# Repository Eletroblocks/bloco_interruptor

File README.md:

# interruptor
PERMITE ou INTERROMPE a transmissão de energia para os blocos seguintes.

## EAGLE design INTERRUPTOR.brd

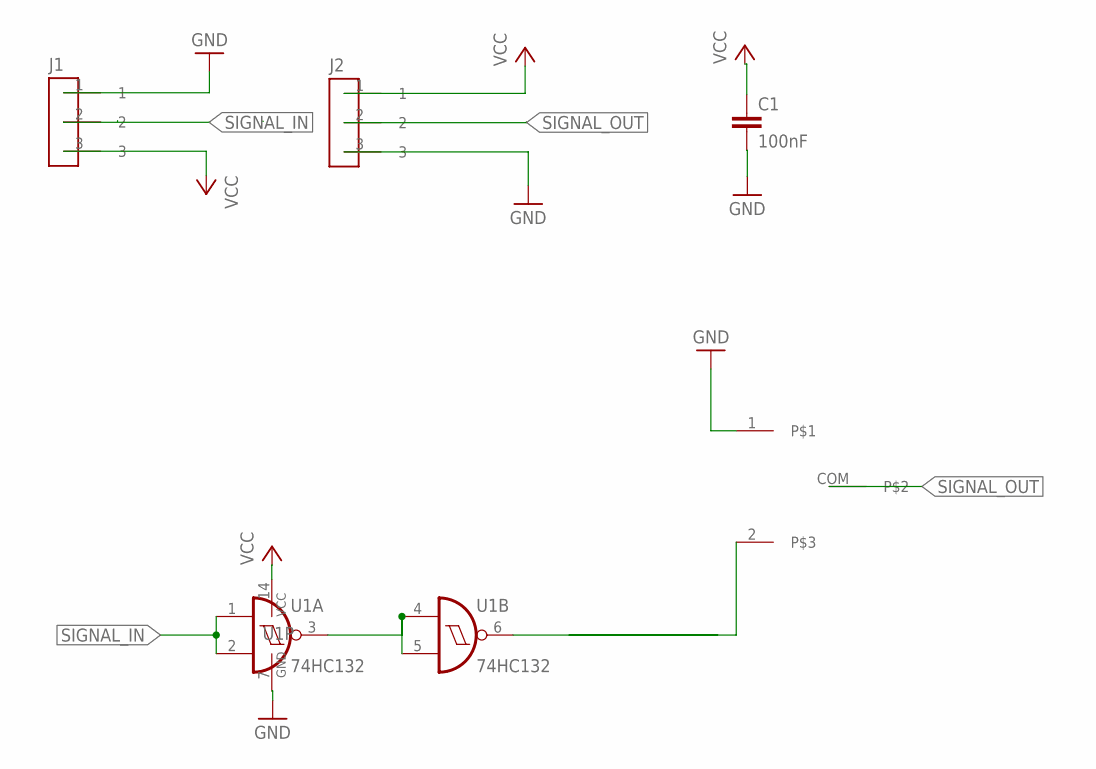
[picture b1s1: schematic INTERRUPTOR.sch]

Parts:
C1: 100nF; C0805
J1: CONECTOR_MACHO; MALE
J2: CONECTOR_FEMEA; FEMALE
J3: SS12F46
U1: 74HC132; SO14

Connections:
GND: C1.2, J1.1, J2.3, J3.1, U1.7 (GND)
unnamed: U1.3 (O), U1.4 (I0), U1.5 (I1)
unnamed: J3.2, U1.6 (O)
SIGNAL_IN: J1.2, U1.1 (I0), U1.2 (I1)
SIGNAL_OUT: J2.2, J3.COM
VCC: C1.1, J1.3, J2.1, U1.14 (VCC)

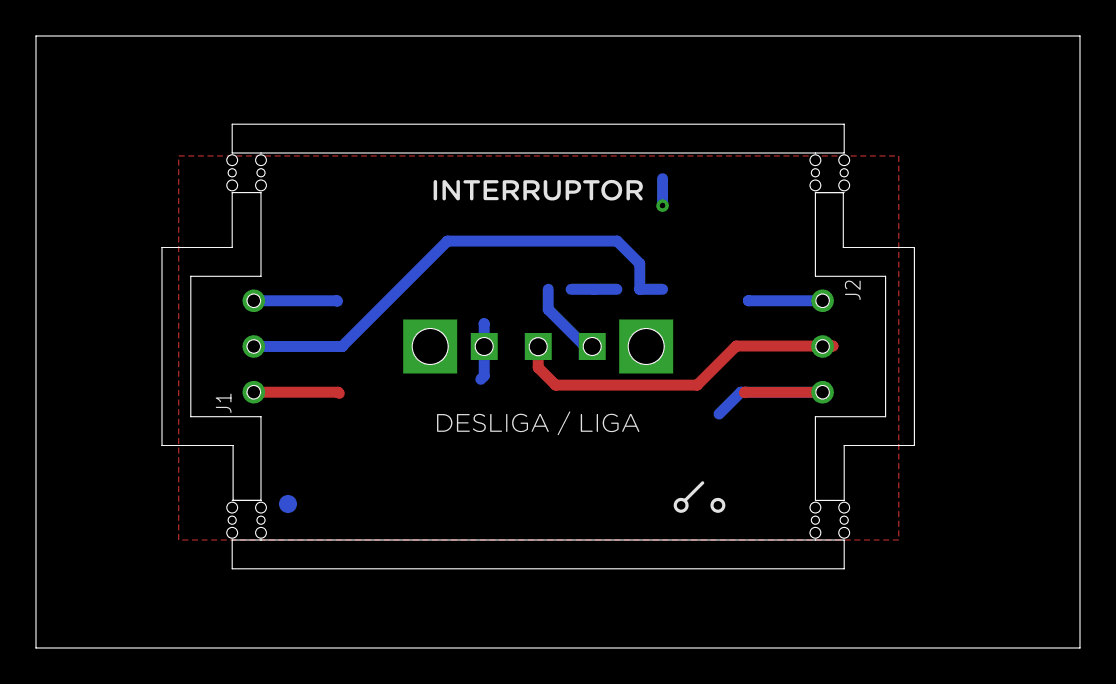
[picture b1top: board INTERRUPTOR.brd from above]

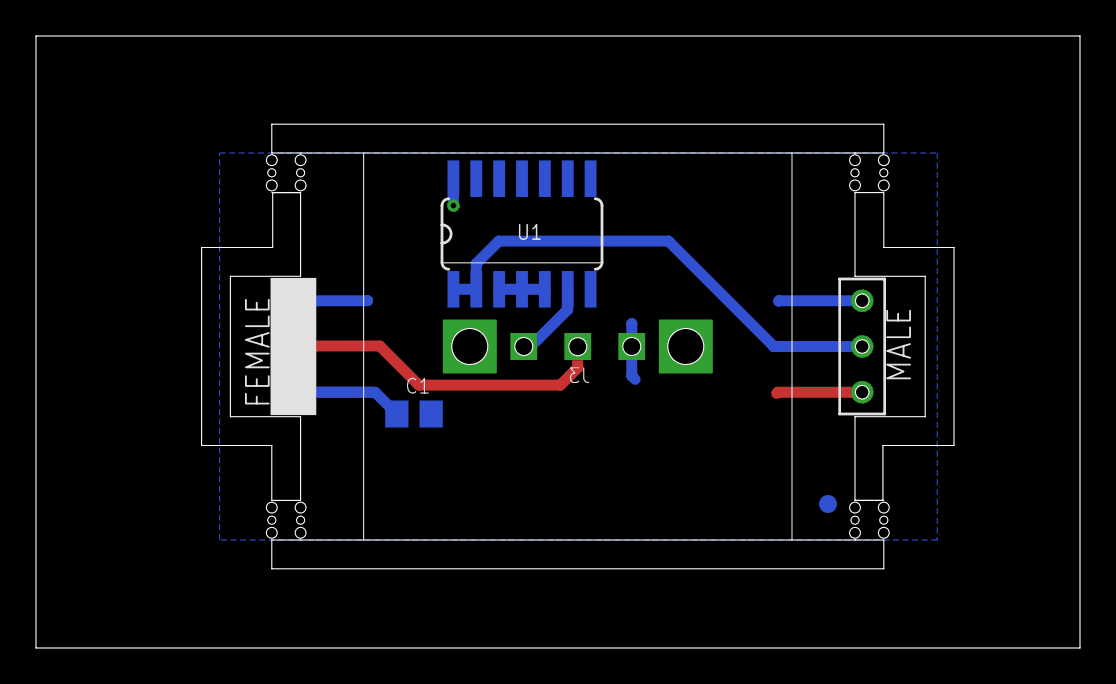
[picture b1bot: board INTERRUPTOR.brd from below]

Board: 2 copper layers, 58.0 x 34.0 mm, 10 parts (3 on the bottom side), 6 nets.

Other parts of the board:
U$1, U$3, U$4, U$5: STAMP_DUPLO
U$2: FIDUCIAL_G10

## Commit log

2020-11-23 init projetct
2020-11-23 correção de pads, adição de label para versionamento e plano de VCC
2020-12-28 organziando arquivos
2020-12-28 imagem
2021-03-11 V1.0.2

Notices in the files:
parts and their libraries:
dicons: Copyright (C) 2004, Bob Starr (rtzaudio@mindspring.com)
